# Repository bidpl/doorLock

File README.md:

# Dorm Fingerprint Door Lock

A fingerprint activated doorlock that maintains key functionality (basically unlock door with finger but key still works if power goes out).

Prototyped with Shiv G. in Fall 2021 ECE 120 Honors lab.

## Control Board

v1.0
Apparently fingerprint sensor doesn't like 5V, it needs 3.3V. I read the documentation for the wrong sensor. Need 3.3V reg and decoupling caps for motor.

v1.1
Added the 3.3V regulator, decoupling caps, seperated logic power from servo power with diode. Added test points and pin 13 led to help with debugging.

## Mounting and Unlock Mechanism

Used a gear with an hourglass cutout to drive the lock spindle. The hourglass cutout gives the spindle enough space to lock and unlock using the key without hitting the gear. However, if driven past the clearance, the gear will still rotate the spindle.

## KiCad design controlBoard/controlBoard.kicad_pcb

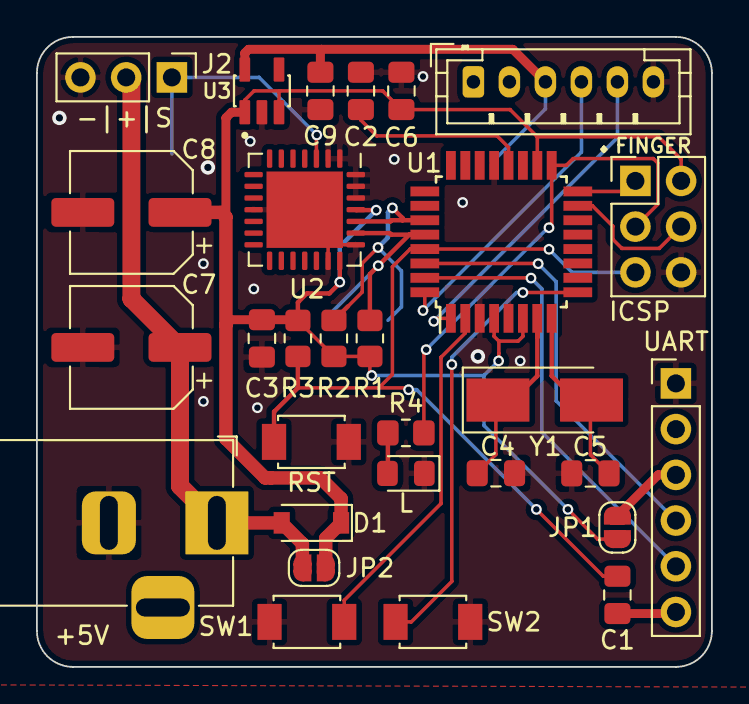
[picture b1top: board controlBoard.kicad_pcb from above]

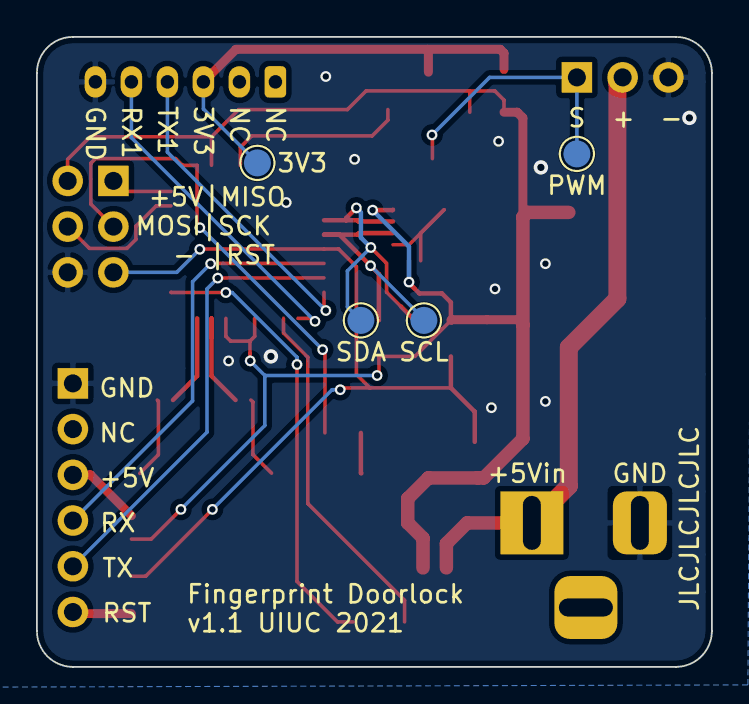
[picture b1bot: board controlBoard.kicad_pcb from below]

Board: 2 copper layers, 37.5 x 35.0 mm, 33 parts (4 on the bottom side), 23 nets.

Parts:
3V3: 3V3; TestPoint_Pad_D1.5mm
+5V: Barrel_Jack_Switch; BarrelJack_Horizontal
C1, C2, C3, C6, C9: 100n; C_0805_2012Metric_Pad1.18x1.45mm_HandSolder
C4, C5: 22p; C_0805_2012Metric_Pad1.18x1.45mm_HandSolder
C7, C8: 47u; CP_Elec_6.3x7.7
D1: D_Schottky; D_SOD-123
FINGER: Fingerprint; JST_PH_B6B-PH-K_1x06_P2.00mm_Vertical
ICSP: ICSP; PinHeader_2x03_P2.54mm_Vertical
J2: Servo; PinHeader_1x03_P2.54mm_Vertical
JP1, JP2: JVCC; SolderJumper-2_P1.3mm_Open_RoundedPad1.0x1.5mm
L: LED; LED_0805_2012Metric_Pad1.15x1.40mm_HandSolder
PWM: PWM; TestPoint_Pad_D1.5mm
R1, R2: 4k7; R_0805_2012Metric_Pad1.20x1.40mm_HandSolder
R3: 10k; R_0805_2012Metric_Pad1.20x1.40mm_HandSolder
R4: 1k; R_0805_2012Metric_Pad1.20x1.40mm_HandSolder
RST: SW_Push; SMD_Pushbutton_3mmx4mm
SCL: SCL; TestPoint_Pad_D1.5mm
SDA: SDA; TestPoint_Pad_D1.5mm
SW1, SW2: SW_Push; SMD_Pushbutton_3mmx4mm
U1: ATmega328P-AU; TQFP-32_7x7mm_P0.8mm
U2: PCA9685BS; QFN-28-1EP_6x6mm_P0.65mm_EP4.25x4.25mm
U3: AP2112K-3.3TRG1; SOT95P285X140-5N
UART: FTDI; PinHeader_1x06_P2.54mm_Vertical
Y1: Crystal; Crystal_SMD_5032-2Pin_5.0x3.2mm_HandSoldering

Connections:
+3V3: 3V3.1, C9.1, FINGER.3, U3.5
+5V: C3.2, C6.2, C8.1, D1.1, ICSP.2, JP1.2, JP2.2, R1.1, R2.1, R3.1, U1.4, U1.6, U1.18, U2.21, U2.25, U3.1, U3.3
+5VA: +5V.1, C7.1, D1.2, J2.2, JP2.1
/MISO: ICSP.1, U1.16
/MOSI: ICSP.4, U1.15
/PWM0: J2.1, PWM.1, U2.3
/Q: SW1.2, U1.2
/Q': SW2.2, U1.9
/RESET: C1.1, ICSP.5, R3.2, RST.1, U1.29
/RX: U1.30, UART.4
/RX1: FINGER.5, U1.1
/SCK: ICSP.3, R4.2, U1.17
/SCL: R1.2, SCL.1, U1.28, U2.23
/SDA: R2.2, SDA.1, U1.27, U2.24
/TX: U1.31, UART.5
/TX1: FINGER.4, U1.32
/XTAL+: C4.1, U1.7, Y1.1
/XTAL-: C5.1, U1.8, Y1.2
GND: +5V.2, C2.2, C3.1, C4.2, C5.2, C6.1, C7.2, C8.2, C9.2, FINGER.6, ICSP.6, J2.3, L.1, RST.2, SW1.1, SW2.1, U1.3, U1.5, U1.21, U2.1, U2.2, U2.11, U2.20, U2.22, U2.26, U2.27, U2.28, U2.29, U3.2, UART.1
unnamed: C1.2, UART.6
unnamed: C2.1, U1.20
unnamed: L.2, R4.1
unnamed: JP1.1, UART.3

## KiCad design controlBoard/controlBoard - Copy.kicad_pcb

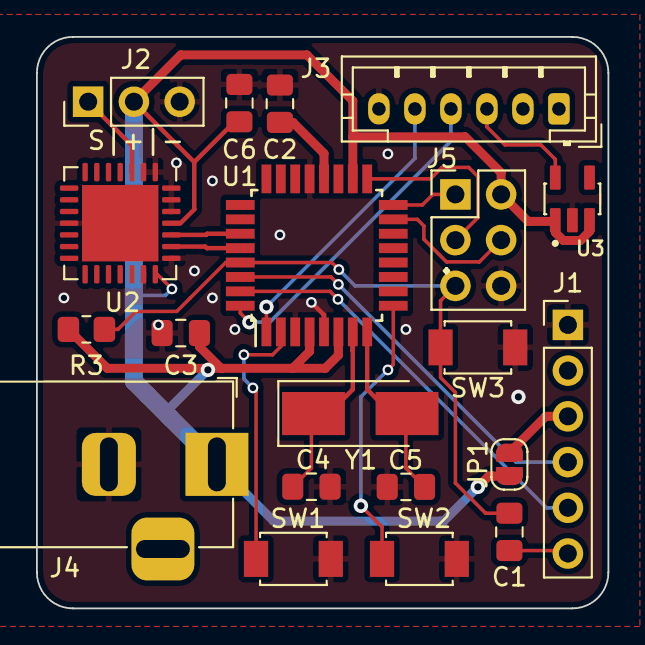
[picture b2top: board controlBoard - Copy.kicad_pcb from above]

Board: 2 copper layers, 31.8 x 31.8 mm, 20 parts (0 on the bottom side), 21 nets.

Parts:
C1, C2, C3, C6: 100n; C_0805_2012Metric_Pad1.18x1.45mm_HandSolder
C4, C5: 22p; C_0805_2012Metric_Pad1.18x1.45mm_HandSolder
J1: FTDI; PinHeader_1x06_P2.54mm_Vertical
J2: Servo; PinHeader_1x03_P2.54mm_Vertical
J3: Fingerprint; JST_PH_B6B-PH-K_1x06_P2.00mm_Vertical
J4: Barrel_Jack_Switch; BarrelJack_Horizontal
J5: ICSP; PinHeader_2x03_P2.54mm_Vertical
JP1: JVCC; SolderJumper-2_P1.3mm_Open_RoundedPad1.0x1.5mm
R3: 10k; R_0805_2012Metric_Pad1.20x1.40mm_HandSolder
SW1, SW2, SW3: SW_Push; SMD_Pushbutton_3mmx4mm
U1: ATmega328P-AU; TQFP-32_7x7mm_P0.8mm
U2: PCA9685BS; QFN-28-1EP_6x6mm_P0.65mm_EP4.25x4.25mm
U3: AP2112K-3.3TRG1; SOT95P285X140-5N
Y1: Crystal; Crystal_SMD_5032-2Pin_5.0x3.2mm_HandSoldering

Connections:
+5V: C3.2, C6.2, J2.2, J4.1, J5.2, JP1.2, R3.1, U1.4, U1.6, U1.18, U2.21, U2.25, U3.1, U3.3
/MISO: J5.1, U1.16
/MOSI: J5.4, U1.15
/PWM0: J2.1, U2.3
/Q: SW1.2, U1.2
/Q': SW2.2, U1.9
/RESET: C1.1, J5.5, R3.2, SW3.1, U1.29
/RX: J1.4, U1.30
/RX1: J3.5, U1.1
/SCK: J5.3, U1.17
/SCL: U1.28, U2.23
/SDA: U1.27, U2.24
/TX: J1.5, U1.31
/TX1: J3.4, U1.32
/XTAL+: C4.1, U1.7, Y1.1
/XTAL-: C5.1, U1.8, Y1.2
GND: C2.2, C3.1, C4.2, C5.2, C6.1, J1.1, J2.3, J3.6, J4.2, J5.6, SW1.1, SW2.1, SW3.2, U1.3, U1.5, U1.21, U2.1, U2.2, U2.11, U2.20, U2.22, U2.26, U2.27, U2.28, U2.29, U3.2
unnamed: C1.2, J1.6
unnamed: C2.1, U1.20
unnamed: J1.3, JP1.1
unnamed: J3.3, U3.5

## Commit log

2021-12-10 Tested arduino to arduino i2c communication
2021-12-15 Fixed test serialToI2C.ino and added kicad files
2021-12-17 Added button footprint and layout pcb
2021-12-21 Swapped TX1 and RX1 pins, cleaned up board a bit to send off to production
2022-01-01 Added 2 electrolytic caps, pin 13 led, 3v3 linear reg, seperated power for logic and servo, increased board size, rotated some headers, added some test points
2022-01-12 Added decoupling cap for fingerprint reader, generated gerbers
2022-01-18 Added 3d footprints to pcb, edited README.md
2022-01-19 v1.0 firmware (it sorta work)
2022-01-20 Ported boardfirmware to new fingerprint sensor (doorlockFirmware-v1.1), only tested on breadboard
